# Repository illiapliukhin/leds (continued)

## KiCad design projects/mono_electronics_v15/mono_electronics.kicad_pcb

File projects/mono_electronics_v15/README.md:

# mono_electronics v15b: ESP32-S3 mono LED driver board (standalone KiCad project)

This folder is the self-contained, canonical copy of the v15 mono electronics board (PR #4). Open `mono_electronics.kicad_pro` in KiCad 10. The symbols (`symbols/`), footprints (`footprints/mono_electronics.pretty`) and 3D models (`3dmodels/`, via `${KIPRJMOD}`) are all local. The originals stay in `hardware/mono_schematic/` (schematic) and `hardware/mono_electronics/` (board), and are kept in sync.

## Spec summary
| | |
|---|---|
| Board | 148.0 × 99.5 mm, 4 layers, **1.6 mm JLC04161H-7628** (1 oz outer / 0.5 oz inner, ENIG), top-side assembly only, 4 × M2.5 plated holes, 3 fiducials |
| MCU | ESP32-S3FN8 (QFN-56), 40 MHz crystal, USB-C (HRO TYPE-C-31-M-12) with USBLC6-2SC6 ESD |
| Power in | USB VBUS_CONN → SMF12A TVS → TPS259531 eFuse (5.7 V OVP, R_ILM 2.7 k = 0.78 A) → BQ25185 charger/power path (ILIM 18 k ≈ 0.475 A, ISET 620 R) |
| Battery | 1S Li-ion on JST PH S3B-PH-SM4-TB; 0466002 2 A fuse; AO3401A reverse-battery P-FET; MAX17048 gauge |
| Rails | LED_4V1 = 4.24 V (TPS63802, FB 681k/91k); AON_3V3 (TLV75733P); LED_LOGIC_3V3 / AUDIO_3V3 (TPS22917 switches) |
| LED drive | 2 × MBI5124 (16 ch, 10 mA, Rext 1.82 k), 2 × 74HC154 row decoders, 32 × AO3403 row FETs, SN74LVC8T245 level shift; worst row drop ≈ 107 mV |
| Interfaces | 2 × 40-pin 0.5 mm FFC (Type B cable), installation variant: 2 × 2×20 1.27 mm box headers + 64 × PESD5V0S1BL; 4 × RS-485/sync ports (JST SH 6P, THVD1406); BMI270 IMU; MEMS mic |
| LED interface | See `docs/LED_INTERFACE_STANDARD.md` |

## Contents
- `mono_electronics.kicad_pro / .kicad_sch / .kicad_pcb`, `sheets/` (10 sub-sheets), `symbols/`, `footprints/`, `3dmodels/`, `sym-lib-table`, `fp-lib-table`
- `fab/`: Gerbers and Excellon drill (`fab/gerbers/`), JLCPCB BOM + CPL for the **wearable** and **installation** variants, annotated BOM, `README_FAB.md`, and `mono_electronics_v15_fab.zip` (the upload package)
- `drawings/`: schematic PDF, top assembly drawing PDF
- `renders/`: top / bottom / iso 3D renders
- `docs/`: MFG_AUDIT_v15 (manufacturing-standards audit and fixes), ABSMAX_REVIEW_v13, LED_INTERFACE_STANDARD, REWORK_LOG, LAST_CHANGES, PROZVONKA_v15 (continuity check), ERC_WAIVERS

## Verification (2026-10-12, KiCad 10.0.7 kicad-cli, run from this folder)
- `kicad-cli pcb drc --schematic-parity --severity-all mono_electronics.kicad_pcb`: **0 violations, 0 unconnected, 0 parity issues**. Board min clearance rule 0.127 mm. Zones refilled before plotting.
- `kicad-cli sch erc --severity-all mono_electronics.kicad_sch`: **0**
- Continuity 312/312 footprints (309 schematic parts + 3 board-only fiducials). Nets 224. All trace bends are arcs. No B-side parts.

## Known gaps
- No 3D model for J_BAT1 (JST S3B-PH-SM4-TB): there is none in the KiCad library.
- J_RH1/J_CH1 box header C42462832: stock ~125, so check it before ordering. Thin stock also on MIC1, Y1 and J_BAT1 (see fab/README_FAB.md).
- Check CPL rotations in the JLC preview: the CPL is raw KiCad output, with no JLC offsets applied.

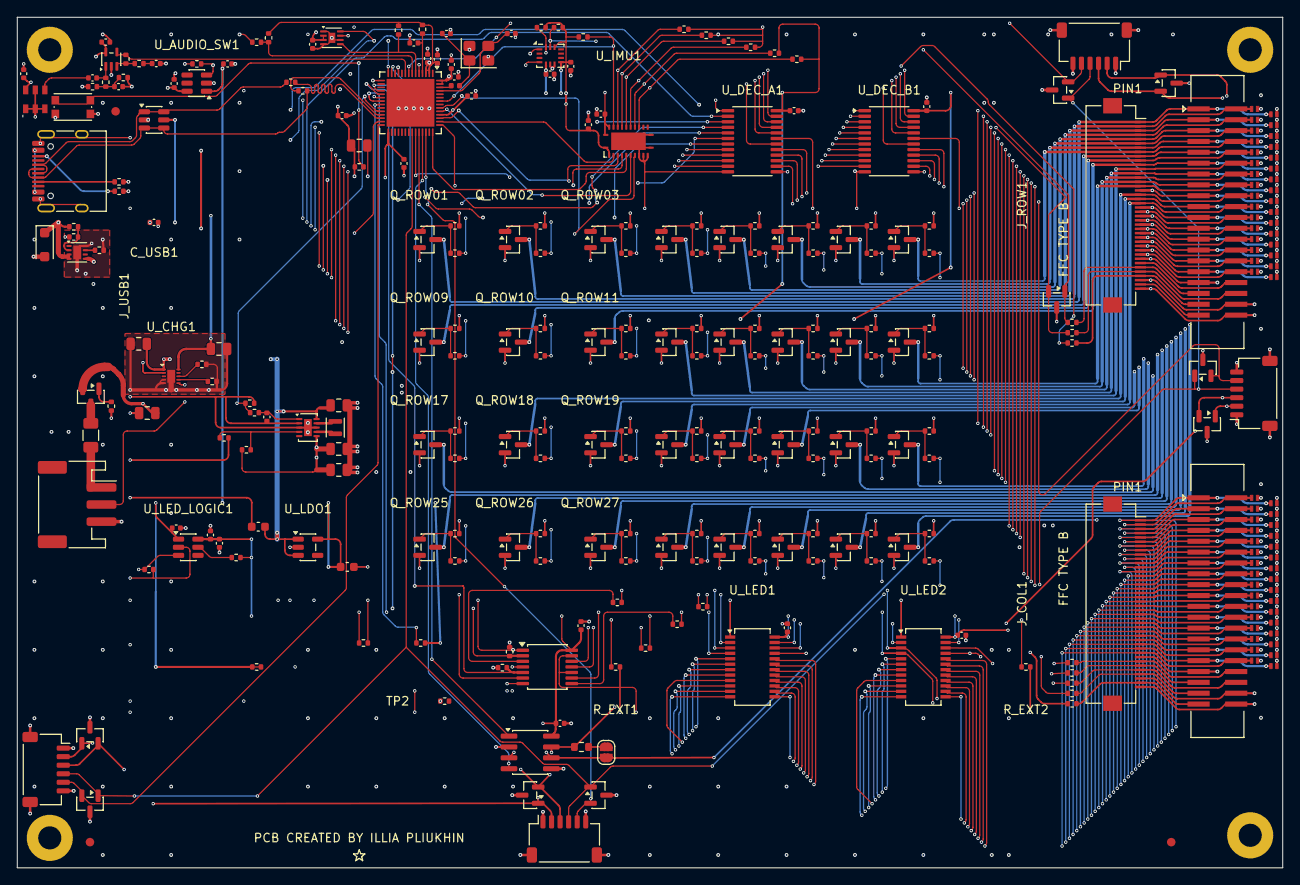
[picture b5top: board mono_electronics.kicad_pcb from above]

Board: 4 copper layers, 148.0 x 99.5 mm, 312 parts (0 on the bottom side), 223 nets.

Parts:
C_485: 100nF; C_0402_1005Metric
C_AC1: 1u; C_0402_1005Metric
C_ASW_IN1: 1u; C_0402_1005Metric
C_AUD1: 100n; C_0402_1005Metric
C_AUD_SW1: 1u; C_0402_1005Metric
C_B1: 4.7u; C_0402_1005Metric
C_BUF_V1: 100n; C_0402_1005Metric
C_CHG_BAT1: 10u; C_0805_2012Metric
C_CHG_IN1: 10u; C_0805_2012Metric
C_CHG_SYS1: 10u; C_0805_2012Metric
C_CHIP_PU1: 1u; C_0402_1005Metric
C_DECA_V1: 100n; C_0402_1005Metric
C_DECB_V1: 100n; C_0402_1005Metric
C_EN1: 10n; C_0402_1005Metric
C_GAUGE1: 100n; C_0402_1005Metric
C_GN1: 4.7u; C_0402_1005Metric
C_IMU_VDD1: 100n; C_0402_1005Metric
C_IMU_VIO1: 100n; C_0402_1005Metric
C_LDO_IN1: 1u; C_0603_1608Metric
C_LDO_OUT1: 1u; C_0603_1608Metric
C_LED1, C_LED2: 22u; C_0805_2012Metric
C_LED1_V1, C_LED2_V1: 100n; C_0402_1005Metric
C_LL1: 1u; C_0402_1005Metric
C_LL2: 100n; C_0402_1005Metric
C_LL_IN1: 1u; C_0402_1005Metric_SilkTrim
C_MCU1: 22u; C_0805_2012Metric
C_MCU_A2: 1u; C_0402_1005Metric
C_MCU_A3: 100n; C_0402_1005Metric
C_MCU_CPU1: 100n; C_0402_1005Metric
C_MCU_DA1: 100n; C_0402_1005Metric
C_MCU_DA2: 1u; C_0402_1005Metric
C_MCU_RTC1: 100n; C_0402_1005Metric
C_MCU_SPI1: 1u; C_0402_1005Metric
C_MIC1: 100n; C_0402_1005Metric
C_SYS1: 10u; C_0805_2012Metric
C_USB1: 100n; C_0402_1005Metric
C_XLAT_A1: 100n; C_0402_1005Metric
C_XLAT_B1: 100n; C_0402_1005Metric
C_XTAL1, C_XTAL2: 10p; C_0402_1005Metric
D_C01, D_C02, D_C03, D_C04, D_C05, D_C06, D_C07, D_C08, D_C09, D_C10, D_C11, D_C12, D_C13, D_C14, D_C15, D_C16, D_C17, D_C18, D_C19, D_C20, D_C21, D_C22, D_C23, D_C24, D_C25, D_C26, D_C27, D_C28, D_C29, D_C30, D_C31, D_C32: PESD5V0S1BL (DNP wearable); D_SOD-882
D_E_AB1: SM712; SOT-23
D_E_SP1: PESD3V3S2UT; SOT-23
D_ID1: PESD5V0S2BT; SOT-23
D_N_AB1: SM712; SOT-23
D_N_SP1: PESD3V3S2UT; SOT-23
D_R01, D_R02, D_R03, D_R04, D_R05, D_R06, D_R07, D_R08, D_R09, D_R10, D_R11, D_R12, D_R13, D_R14, D_R15, D_R16, D_R17, D_R18, D_R19, D_R20, D_R21, D_R22, D_R23, D_R24, D_R25, D_R26, D_R27, D_R28, D_R29, D_R30, D_R31, D_R32: PESD5V0S1BL (DNP wearable); D_SOD-882
D_S_AB1: SM712; SOT-23
D_S_SP1: PESD3V3S2UT; SOT-23
D_VBUS1: SMF12A; D_SOD-123F
D_W_AB1: SM712; SOT-23
D_W_SP1: PESD3V3S2UT; SOT-23
FID1, FID2, FID3: Fiducial; Fiducial_1mm_Mask2mm
F_BAT1: 0466002.NRHF 2A; Fuse_1206_3216Metric
H1, H2, H3, H4: M2.5; MountingHole_2.7mm_M2.5_Pad
JP_TERM1: TERM; SolderJumper-2_P1.3mm_Open_RoundedPad1.0x1.5mm
J_BAT1: S3B-PH-SM4-TB; JST_PH_S3B-PH-SM4-TB_1x03-1MP_P2.00mm_Horizontal
J_CH1: BH127VS-40P-H49 2x20 1.27mm box header (DNP weara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; BoxHeader_XFCN_BH127VS-40P-H49_2x20_P1.27mm_Vertical_SMD
J_COL1: FFC_40P_050_COL
J_PORT_E1: SM06B-SRSS-TB; JST_SH_SM06B-SRSS-TB_1x06-1MP_P1.00mm_Horizontal
J_PORT_N1: SM06B-SRSS-TB; JST_SH_SM06B-SRSS-TB_1x06-1MP_P1.00mm_Horizontal
J_PORT_S1: SM06B-SRSS-TB; JST_SH_SM06B-SRSS-TB_1x06-1MP_P1.00mm_Horizontal
J_PORT_W1: SM06B-SRSS-TB; JST_SH_SM06B-SRSS-TB_1x06-1MP_P1.00mm_Horizontal
J_RH1: BH127VS-40P-H49 2x20 1.27mm box header (DNP weara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; BoxHeader_XFCN_BH127VS-40P-H49_2x20_P1.27mm_Vertical_SMD
J_ROW1: FFC_40P_050_ROW
J_USB1: TYPE-C-31-M-12; USB_C_Receptacle_HRO_TYPE-C-31-M-12
L_LED1: DFE201612E-R47M; L_Murata_DFE201610P
L_XTAL1: 24nH; L_0402_1005Metric
MIC1: MA-HFA381-H13-1AF; MIC_Gettop_MA-HFA381_3.5x2.65mm
Q_BAT1: AO3401A; SOT-23
Q_ROW01, Q_ROW02, Q_ROW03, Q_ROW04, Q_ROW05, Q_ROW06, Q_ROW07, Q_ROW08, Q_ROW09, Q_ROW10, Q_ROW11, Q_ROW12, Q_ROW13, Q_ROW14, Q_ROW15, Q_ROW16, Q_ROW17, Q_ROW18, Q_ROW19, Q_ROW20, Q_ROW21, Q_ROW22, Q_ROW23, Q_ROW24, Q_ROW25, Q_ROW26, Q_ROW27, Q_ROW28, Q_ROW29, Q_ROW30, Q_ROW31, Q_ROW32: AO3403; SOT-23
R_ADDR0, R_ADDR1, R_ADDR2, R_ADDR3: 100k; R_0402_1005Metric
R_ALRT1: 10k; R_0402_1005Metric
R_AUD_PD1: 100k; R_0402_1005Metric
R_B1, R_B2: 100k; R_0402_1005Metric
R_BATG1: 10k; R_0402_1005Metric
R_BOOT0: 10k; R_0402_1005Metric
R_CC1, R_CC2: 5.1k; R_0402_1005Metric
R_CHIP_PU1: 10k; R_0402_1005Metric
R_CLK_PD1: 100k; R_0402_1005Metric
R_CLK_SER1: 22R; R_0402_1005Metric
R_ENA1: 47k; R_0402_1005Metric
R_ENB1: 47k; R_0402_1005Metric
R_EN_BOT1: 39k; R_0402_1005Metric
R_EN_PD1: 100k; R_0402_1005Metric
R_EN_SER1: 100k; R_0402_1005Metric
R_EN_TOP1: 100k; R_0402_1005Metric
R_EXP_3V1: 0R DNP; R_0402_1005Metric
R_EXP_CLK1: 33R DNP; R_0402_1005Metric
R_EXP_LE1: 33R DNP; R_0402_1005Metric
R_EXP_OE1: 33R DNP; R_0402_1005Metric
R_EXP_SDI1: 33R DNP; R_0402_1005Metric
R_EXT1, R_EXT2: 1.82k; R_0402_1005Metric
R_F1: 100k; R_0402_1005Metric_SilkTrim
R_FB_BOT1: 91k; R_0402_1005Metric
R_FB_TOP1: 681k; R_0402_1005Metric
R_G01, R_G02, R_G03, R_G04, R_G05, R_G06, R_G07, R_G08, R_G09, R_G10, R_G11, R_G12, R_G13, R_G14, R_G15, R_G16, R_G17, R_G18, R_G19, R_G20, R_G21, R_G22, R_G23, R_G24, R_G25, R_G26, R_G27, R_G28, R_G29, R_G30, R_G31, R_G32: 33R; R_0402_1005Metric
R_GN1: 2.2k; R_0402_1005Metric
R_ID_3V1: 100R; R_0402_1005Metric
R_ID_SCL1: 33R; R_0402_1005Metric
R_ID_SDA1: 33R; R_0402_1005Metric
R_ILIM1: 18k; R_0402_1005Metric
R_ILM1: 2.7k; R_0402_1005Metric
R_INB1: 100k; R_0402_1005Metric
R_ISET1: 600R; R_0402_1005Metric
R_LE_PD1: 100k; R_0402_1005Metric
R_LE_SER1: 22R; R_0402_1005Metric
R_LOGIC_PD1: 100k; R_0402_1005Metric
R_OE_PU1: 47k; R_0402_1005Metric
R_OE_YPU1: 47k; R_0402_1005Metric
R_PU01, R_PU02, R_PU03, R_PU04, R_PU05, R_PU06, R_PU07, R_PU08, R_PU09, R_PU10, R_PU11, R_PU12, R_PU13, R_PU14, R_PU15, R_PU16, R_PU17, R_PU18, R_PU19, R_PU20, R_PU21, R_PU22, R_PU23, R_PU24, R_PU25, R_PU26, R_PU27, R_PU28, R_PU29, R_PU30, R_PU31, R_PU32: 47k; R_0402_1005Metric
R_QOD1: 1k; R_0402_1005Metric
R_SCL1: 4.7k; R_0402_1005Metric
R_SDA1: 4.7k; R_0402_1005Metric
R_SDI_PD1: 100k; R_0402_1005Metric
R_SDI_SER1: 22R; R_0402_1005Metric
R_TERM1: 120R; R_0603_1608Metric
R_TH1: 10k 1%; R_0402_1005Metric
R_USB_N1: 22R; R_0402_1005Metric
R_USB_P1: 22R; R_0402_1005Metric
R_XOE1: 10k; R_0402_1005Metric
SW1: KMR2; SW_Push_1P1T_NO_CK_KMR2
TH_PCB1: NTC 10k B3435; R_0402_1005Metric
TP1: AON_3V3; R_0402_1005Metric
TP2: GND; R_0402_1005Metric
U1: ESP32-S3FN8; QFN-56-1EP_7x7mm_P0.4mm_EP5.6x5.6mm
U_485: THVD1406DR; SOIC-8_3.9x4.9mm_P1.27mm
U_AUDIO1: TLV9001IDCKR; SOT-353_SC-70-5
U_AUDIO_SW1: TPS22917; SOT-23-6
U_CHG1: BQ25185; Texas_DLH0010A_WSON-10-1EP_2x2mm_P0.4mm_EP0.9x1.5mm
U_DEC_A1: 74HC154; TSSOP-24_4.4x7.8mm_P0.65mm
U_DEC_B1: 74HC154; TSSOP-24_4.4x7.8mm_P0.65mm
U_ESD1: USBLC6-2SC6; SOT-23-6
U_GAUGE1: MAX17048G+T10; TDFN-8-1EP_2x2mm_P0.5mm_EP0.8x1.2mm
U_IMU1: BMI270; Bosch_LGA-14_3x2.5mm_P0.5mm
U_LDO1: TLV75733PDBVR; SOT-23-5
U_LED1, U_LED2: MBI5124GP-B; SSOP-24_3.9x8.7mm_P0.635mm
U_LED_BUF1: SN74LV125A; TSSOP-14_4.4x5mm_P0.65mm
U_LED_LOGIC1: TPS22917; SOT-23-6
U_LED_PWR1: TPS63802DLAR; TDFN-10-1EP_2x3mm_P0.5mm_EP0.9x2mm
U_OVP1: TPS259531DSGR; Texas_DSG0008A_WSON-8-1EP_2x2mm_P0.5mm_EP0.9x1.6mm
U_ROW_XLAT1: SN74LVC8T245RHLR; Texas_RHL0024A_VQFN-24-1EP_3.5x5.5mm_P0.5mm_EP2.05x4.05mm
Y1: L327S400H11L; Crystal_SMD_3225-4Pin_3.2x2.5mm

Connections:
AON_3V3: C_ASW_IN1.1, C_IMU_VDD1.1, C_IMU_VIO1.1, C_LDO_OUT1.1, C_LL_IN1.1, C_MCU1.1, C_MCU_A2.1, C_MCU_A3.1, C_MCU_CPU1.1, C_MCU_DA1.1, C_MCU_DA2.1, C_MCU_RTC1.1, C_MCU_SPI1.1, C_XLAT_A1.1, R_ALRT1.2, R_BOOT0.1, R_CHIP_PU1.2, R_ID_3V1.1, R_OE_PU1.2, R_SCL1.2, R_SDA1.2, R_TH1.2, R_XOE1.1, TP1.1, TP1.2, U1.2, U1.3, U1.20, U1.29, U1.46, U1.55, U1.56, U_AUDIO_SW1.1, U_IMU1.5, U_IMU1.8, U_IMU1.12, U_LDO1.5, U_LED_LOGIC1.1, U_ROW_XLAT1.1, U_ROW_XLAT1.2
AUDIO_3V3: C_AUD1.1, C_AUD_SW1.1, C_MIC1.2, MIC1.6, R_B1.1, U_AUDIO1.5, U_AUDIO_SW1.6
AUDIO_ADC: R_F1.2, U1.9, U_AUDIO1.4
AUDIO_EN: R_AUD_PD1.1, U1.11, U_AUDIO_SW1.3
AUD_BIAS: C_B1.1, R_B1.2, R_B2.1, R_INB1.1
AUD_FB: R_F1.1, R_GN1.1, U_AUDIO1.3
AUD_GC: C_GN1.1, R_GN1.2
AUD_INP: C_AC1.2, R_INB1.2, U_AUDIO1.1
BAT_FUSE: F_BAT1.2, Q_BAT1.3
BAT_GATE: Q_BAT1.1, R_BATG1.1
BAT_PACK: F_BAT1.1, J_BAT1.1
BAT_RAW: C_CHG_BAT1.2, C_GAUGE1.2, Q_BAT1.2, U_CHG1.2, U_GAUGE1.2, U_GAUGE1.3
CHIP_PU: C_CHIP_PU1.1, R_CHIP_PU1.1, U1.4
COL_01: D_C01.1, J_CH1.1, J_COL1.1, U_LED1.5
COL_02: D_C02.1, J_CH1.2, J_COL1.2, U_LED1.6
COL_03: D_C03.1, J_CH1.3, J_COL1.3, U_LED1.7
COL_04: D_C04.1, J_CH1.4, J_COL1.4, U_LED1.8
COL_05: D_C05.1, J_CH1.5, J_COL1.5, U_LED1.9
COL_06: D_C06.1, J_CH1.6, J_COL1.6, U_LED1.10
COL_07: D_C07.1, J_CH1.7, J_COL1.7, U_LED1.11
COL_08: D_C08.1, J_CH1.8, J_COL1.8, U_LED1.12
COL_09: D_C09.1, J_CH1.9, J_COL1.9, U_LED1.13
COL_10: D_C10.1, J_CH1.10, J_COL1.10, U_LED1.14
COL_11: D_C11.1, J_CH1.11, J_COL1.11, U_LED1.15
COL_12: D_C12.1, J_CH1.12, J_COL1.12, U_LED1.16
COL_13: D_C13.1, J_CH1.13, J_COL1.13, U_LED1.17
COL_14: D_C14.1, J_CH1.14, J_COL1.14, U_LED1.18
COL_15: D_C15.1, J_CH1.15, J_COL1.15, U_LED1.19
COL_16: D_C16.1, J_CH1.16, J_COL1.16, U_LED1.20
COL_17: D_C17.1, J_CH1.17, J_COL1.17, U_LED2.5
COL_18: D_C18.1, J_CH1.18, J_COL1.18, U_LED2.6
COL_19: D_C19.1, J_CH1.19, J_COL1.19, U_LED2.7
COL_20: D_C20.1, J_CH1.20, J_COL1.20, U_LED2.8
COL_21: D_C21.1, J_CH1.21, J_COL1.21, U_LED2.9
COL_22: D_C22.1, J_CH1.22, J_COL1.22, U_LED2.10
COL_23: D_C23.1, J_CH1.23, J_COL1.23, U_LED2.11
COL_24: D_C24.1, J_CH1.24, J_COL1.24, U_LED2.12
COL_25: D_C25.1, J_CH1.25, J_COL1.25, U_LED2.13
COL_26: D_C26.1, J_CH1.26, J_COL1.26, U_LED2.14
COL_27: D_C27.1, J_CH1.27, J_COL1.27, U_LED2.15
COL_28: D_C28.1, J_CH1.28, J_COL1.28, U_LED2.16
COL_29: D_C29.1, J_CH1.29, J_COL1.29, U_LED2.17
COL_30: D_C30.1, J_CH1.30, J_COL1.30, U_LED2.18
COL_31: D_C31.1, J_CH1.31, J_COL1.31, U_LED2.19
COL_32: D_C32.1, J_CH1.32, J_COL1.32, U_LED2.20
DEC_A_EN_N: U1.47, U_ROW_XLAT1.7
DEC_A_EN_N_4V: R_ENA1.1, U_DEC_A1.18, U_ROW_XLAT1.17
DEC_B_EN_N: U1.48, U_ROW_XLAT1.8
DEC_B_EN_N_4V: R_ENB1.1, U_DEC_B1.18, U_ROW_XLAT1.16
EXP_3V3: J_CH1.39, J_COL1.39, R_EXP_3V1.2
EXP_CLK: J_CH1.35, J_COL1.35, R_EXP_CLK1.2
EXP_LE: J_CH1.36, J_COL1.36, R_EXP_LE1.2
EXP_OE: J_CH1.37, J_COL1.37, R_EXP_OE1.2
EXP_SDI: J_CH1.34, J_COL1.34, R_EXP_SDI1.2
FRAME_SYNC: D_E_SP1.1, D_N_SP1.1, D_S_SP1.1, D_W_SP1.1, J_PORT_E1.4, J_PORT_N1.4, J_PORT_S1.4, J_PORT_W1.4, U1.36
GAUGE_ALRT_N: R_ALRT1.1, U1.6, U_GAUGE1.5
GND: C_485.2, C_ASW_IN1.2, C_AUD1.2, C_AUD_SW1.2, C_B1.2, C_BUF_V1.2, C_CHG_BAT1.1, C_CHG_IN1.2, C_CHG_SYS1.1, C_CHIP_PU1.2, C_DECA_V1.2, C_DECB_V1.2, C_EN1.2, C_GAUGE1.1, C_GN1.2, C_IMU_VDD1.2, C_IMU_VIO1.2, C_LDO_IN1.1, C_LDO_OUT1.2, C_LED1.2, C_LED1_V1.2, C_LED2.2, C_LED2_V1.2, C_LL1.2, C_LL2.2, C_LL_IN1.2, C_MCU1.2, C_MCU_A2.2, C_MCU_A3.2, C_MCU_CPU1.2, C_MCU_DA1.2, C_MCU_DA2.2, C_MCU_RTC1.2, C_MCU_SPI1.2, C_MIC1.1, C_SYS1.2, C_USB1.2, C_XLAT_A1.2, C_XLAT_B1.2, C_XTAL1.2, C_XTAL2.2, D_C01.2, D_C02.2, D_C03.2, D_C04.2, D_C05.2, D_C06.2, D_C07.2, D_C08.2, D_C09.2, D_C10.2, D_C11.2, D_C12.2, D_C13.2, D_C14.2, D_C15.2, D_C16.2, D_C17.2, D_C18.2, D_C19.2, D_C20.2, D_C21.2, D_C22.2, D_C23.2, D_C24.2, D_C25.2, D_C26.2, D_C27.2, D_C28.2, D_C29.2, D_C30.2, D_C31.2, D_C32.2, D_E_AB1.3, D_E_SP1.3, D_ID1.3, D_N_AB1.3, D_N_SP1.3, D_R01.2, D_R02.2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
GPIO0_BOOT: R_BOOT0.2, SW1.1, U1.5
ID_3V3: J_RH1.37, J_ROW1.37, R_ID_3V1.2
ID_SCL: J_RH1.36, J_ROW1.36, R_ID_SCL1.2
ID_SDA: J_RH1.35, J_ROW1.35, R_ID_SDA1.2
ILIM_VSET: R_ILIM1.1, U_CHG1.7
IMU_INT1: U1.15, U_IMU1.4
IMU_SCL: D_ID1.2, R_ID_SCL1.1, R_SCL1.1, U1.14, U_GAUGE1.7, U_IMU1.13
IMU_SDA: D_ID1.1, R_ID_SDA1.1, R_SDA1.1, U1.13, U_GAUGE1.8, U_IMU1.14
ISET: R_ISET1.1, U_CHG1.8
LED_4V1: C_DECA_V1.1, C_DECB_V1.1, C_LED1.1, C_LED2.1, C_XLAT_B1.1, Q_ROW01.2, Q_ROW02.2, Q_ROW03.2, Q_ROW04.2, Q_ROW05.2, Q_ROW06.2, Q_ROW07.2, Q_ROW08.2, Q_ROW09.2, Q_ROW10.2, Q_ROW11.2, Q_ROW12.2, Q_ROW13.2, Q_ROW14.2, Q_ROW15.2, Q_ROW16.2, Q_ROW17.2, Q_ROW18.2, Q_ROW19.2, Q_ROW20.2, Q_ROW21.2, Q_ROW22.2, Q_ROW23.2, Q_ROW24.2, Q_ROW25.2, Q_ROW26.2, Q_ROW27.2, Q_ROW28.2, Q_ROW29.2, Q_ROW30.2, Q_ROW31.2, Q_ROW32.2, R_ENA1.2, R_ENB1.2, R_FB_TOP1.1, R_PU01.2, R_PU02.2, R_PU03.2, R_PU04.2, R_PU05.2, R_PU06.2, R_PU07.2, R_PU08.2, R_PU09.2, R_PU10.2, R_PU11.2, R_PU12.2, R_PU13.2, R_PU14.2, R_PU15.2, R_PU16.2, R_PU17.2, R_PU18.2, R_PU19.2, R_PU20.2, R_PU21.2, R_PU22.2, R_PU23.2, R_PU24.2, R_PU25.2, R_PU26.2, R_PU27.2, R_PU28.2, R_PU29.2, R_PU30.2, R_PU31.2, R_PU32.2, U_DEC_A1.24, U_DEC_B1.24, U_LED_PWR1.6, U_ROW_XLAT1.23, U_ROW_XLAT1.24
LED_CLK: R_CLK_PD1.1, U1.18, U_LED_BUF1.2
LED_CLK_PRE: R_CLK_SER1.1, U_LED_BUF1.3
LED_CLK_Y: R_CLK_SER1.2, R_EXP_CLK1.1, U_LED1.3, U_LED2.3
LED_EN: R_EN_PD1.1, R_EN_SER1.1, U1.24
LED_EN_RC: C_EN1.1, R_EN_SER1.2, U_LED_PWR1.1
LED_FB: R_FB_BOT1.1, R_FB_TOP1.2, U_LED_PWR1.4
LED_LE: R_LE_PD1.1, U1.21, U_LED_BUF1.9
LED_LE_PRE: R_LE_SER1.1, U_LED_BUF1.8
LED_LE_Y: R_EXP_LE1.1, R_LE_SER1.2, U_LED1.4, U_LED2.4
LED_LOGIC_3V3: C_485.1, C_BUF_V1.1, C_LED1_V1.1, C_LED2_V1.1, C_LL1.1, C_LL2.1, R_EXP_3V1.1, R_OE_YPU1.2, R_QOD1.2, U_485.3, U_485.8, U_LED1.24, U_LED2.24, U_LED_BUF1.14, U_LED_LOGIC1.6
LED_LOGIC_EN: R_LOGIC_PD1.1, U1.27, U_LED_LOGIC1.3
LED_OE_N: R_OE_PU1.1, U1.22, U_LED_BUF1.12
LED_OE_Y: R_EXP_OE1.1, R_OE_YPU1.1, U_LED1.21, U_LED2.21, U_LED_BUF1.11
LED_QOD: R_QOD1.1, U_LED_LOGIC1.5
LED_SDI: R_SDI_PD1.1, U1.19, U_LED_BUF1.5
LED_SDI_PRE: R_SDI_SER1.1, U_LED_BUF1.6
LED_SDI_Y: R_SDI_SER1.2, U_LED1.2
LED_SDO: U_LED1.22, U_LED2.2
LED_SDO2: R_EXP_SDI1.1, U_LED2.22
MIC_OUT: C_AC1.1, MIC1.4
OVP_EN: R_EN_BOT1.1, R_EN_TOP1.2, U_OVP1.2
OVP_ILM: R_ILM1.1, U_OVP1.7
PRES_E: D_E_SP1.2, J_PORT_E1.5, U1.37
PRES_N: D_N_SP1.2, J_PORT_N1.5, U1.8
PRES_S: D_S_SP1.2, J_PORT_S1.5, U1.40
PRES_W: D_W_SP1.2, J_PORT_W1.5, U1.28
REXT1: R_EXT1.1, U_LED1.23
REXT2: R_EXT2.1, U_LED2.23
ROW_01_ANODE: D_R01.1, J_RH1.1, J_ROW1.1, Q_ROW01.3
ROW_01_GATE: Q_ROW01.1, R_G01.1, R_PU01.1
ROW_01_Y: R_G01.2, U_DEC_A1.1
ROW_02_ANODE: D_R02.1, J_RH1.2, J_ROW1.2, Q_ROW02.3
ROW_02_GATE: Q_ROW02.1, R_G02.1, R_PU02.1
ROW_02_Y: R_G02.2, U_DEC_A1.2
ROW_03_ANODE: D_R03.1, J_RH1.3, J_ROW1.3, Q_ROW03.3
ROW_03_GATE: Q_ROW03.1, R_G03.1, R_PU03.1
ROW_03_Y: R_G03.2, U_DEC_A1.3
ROW_04_ANODE: D_R04.1, J_RH1.4, J_ROW1.4, Q_ROW04.3
ROW_04_GATE: Q_ROW04.1, R_G04.1, R_PU04.1
ROW_04_Y: R_G04.2, U_DEC_A1.4
ROW_05_ANODE: D_R05.1, J_RH1.5, J_ROW1.5, Q_ROW05.3
ROW_05_GATE: Q_ROW05.1, R_G05.1, R_PU05.1
ROW_05_Y: R_G05.2, U_DEC_A1.5
ROW_06_ANODE: D_R06.1, J_RH1.6, J_ROW1.6, Q_ROW06.3
ROW_06_GATE: Q_ROW06.1, R_G06.1, R_PU06.1
ROW_06_Y: R_G06.2, U_DEC_A1.6
ROW_07_ANODE: D_R07.1, J_RH1.7, J_ROW1.7, Q_ROW07.3
ROW_07_GATE: Q_ROW07.1, R_G07.1, R_PU07.1
ROW_07_Y: R_G07.2, U_DEC_A1.7
ROW_08_ANODE: D_R08.1, J_RH1.8, J_ROW1.8, Q_ROW08.3
ROW_08_GATE: Q_ROW08.1, R_G08.1, R_PU08.1
ROW_08_Y: R_G08.2, U_DEC_A1.8
ROW_09_ANODE: D_R09.1, J_RH1.9, J_ROW1.9, Q_ROW09.3
ROW_09_GATE: Q_ROW09.1, R_G09.1, R_PU09.1
ROW_09_Y: R_G09.2, U_DEC_A1.9
ROW_10_ANODE: D_R10.1, J_RH1.10, J_ROW1.10, Q_ROW10.3
ROW_10_GATE: Q_ROW10.1, R_G10.1, R_PU10.1
ROW_10_Y: R_G10.2, U_DEC_A1.10
ROW_11_ANODE: D_R11.1, J_RH1.11, J_ROW1.11, Q_ROW11.3
ROW_11_GATE: Q_ROW11.1, R_G11.1, R_PU11.1
ROW_11_Y: R_G11.2, U_DEC_A1.11
ROW_12_ANODE: D_R12.1, J_RH1.12, J_ROW1.12, Q_ROW12.3
ROW_12_GATE: Q_ROW12.1, R_G12.1, R_PU12.1
ROW_12_Y: R_G12.2, U_DEC_A1.13
ROW_13_ANODE: D_R13.1, J_RH1.13, J_ROW1.13, Q_ROW13.3
ROW_13_GATE: Q_ROW13.1, R_G13.1, R_PU13.1
ROW_13_Y: R_G13.2, U_DEC_A1.14
ROW_14_ANODE: D_R14.1, J_RH1.14, J_ROW1.14, Q_ROW14.3
ROW_14_GATE: Q_ROW14.1, R_G14.1, R_PU14.1
ROW_14_Y: R_G14.2, U_DEC_A1.15
ROW_15_ANODE: D_R15.1, J_RH1.15, J_ROW1.15, Q_ROW15.3
ROW_15_GATE: Q_ROW15.1, R_G15.1, R_PU15.1
ROW_15_Y: R_G15.2, U_DEC_A1.16
ROW_16_ANODE: D_R16.1, J_RH1.16, J_ROW1.16, Q_ROW16.3
ROW_16_GATE: Q_ROW16.1, R_G16.1, R_PU16.1
ROW_16_Y: R_G16.2, U_DEC_A1.17
ROW_17_ANODE: D_R17.1, J_RH1.17, J_ROW1.17, Q_ROW17.3
ROW_17_GATE: Q_ROW17.1, R_G17.1, R_PU17.1
ROW_17_Y: R_G17.2, U_DEC_B1.1
ROW_18_ANODE: D_R18.1, J_RH1.18, J_ROW1.18, Q_ROW18.3
ROW_18_GATE: Q_ROW18.1, R_G18.1, R_PU18.1
ROW_18_Y: R_G18.2, U_DEC_B1.2
ROW_19_ANODE: D_R19.1, J_RH1.19, J_ROW1.19, Q_ROW19.3
ROW_19_GATE: Q_ROW19.1, R_G19.1, R_PU19.1
ROW_19_Y: R_G19.2, U_DEC_B1.3
ROW_20_ANODE: D_R20.1, J_RH1.20, J_ROW1.20, Q_ROW20.3
ROW_20_GATE: Q_ROW20.1, R_G20.1, R_PU20.1
ROW_20_Y: R_G20.2, U_DEC_B1.4
ROW_21_ANODE: D_R21.1, J_RH1.21, J_ROW1.21, Q_ROW21.3
ROW_21_GATE: Q_ROW21.1, R_G21.1, R_PU21.1
ROW_21_Y: R_G21.2, U_DEC_B1.5
ROW_22_ANODE: D_R22.1, J_RH1.22, J_ROW1.22, Q_ROW22.3
ROW_22_GATE: Q_ROW22.1, R_G22.1, R_PU22.1
ROW_22_Y: R_G22.2, U_DEC_B1.6
ROW_23_ANODE: D_R23.1, J_RH1.23, J_ROW1.23, Q_ROW23.3
ROW_23_GATE: Q_ROW23.1, R_G23.1, R_PU23.1
ROW_23_Y: R_G23.2, U_DEC_B1.7
ROW_24_ANODE: D_R24.1, J_RH1.24, J_ROW1.24, Q_ROW24.3
ROW_24_GATE: Q_ROW24.1, R_G24.1, R_PU24.1
ROW_24_Y: R_G24.2, U_DEC_B1.8
ROW_25_ANODE: D_R25.1, J_RH1.25, J_ROW1.25, Q_ROW25.3
ROW_25_GATE: Q_ROW25.1, R_G25.1, R_PU25.1
ROW_25_Y: R_G25.2, U_DEC_B1.9
ROW_26_ANODE: D_R26.1, J_RH1.26, J_ROW1.26, Q_ROW26.3
ROW_26_GATE: Q_ROW26.1, R_G26.1, R_PU26.1
ROW_26_Y: R_G26.2, U_DEC_B1.10
ROW_27_ANODE: D_R27.1, J_RH1.27, J_ROW1.27, Q_ROW27.3
ROW_27_GATE: Q_ROW27.1, R_G27.1, R_PU27.1
ROW_27_Y: R_G27.2, U_DEC_B1.11
ROW_28_ANODE: D_R28.1, J_RH1.28, J_ROW1.28, Q_ROW28.3
ROW_28_GATE: Q_ROW28.1, R_G28.1, R_PU28.1
ROW_28_Y: R_G28.2, U_DEC_B1.13
ROW_29_ANODE: D_R29.1, J_RH1.29, J_ROW1.29, Q_ROW29.3
ROW_29_GATE: Q_ROW29.1, R_G29.1, R_PU29.1
ROW_29_Y: R_G29.2, U_DEC_B1.14
ROW_30_ANODE: D_R30.1, J_RH1.30, J_ROW1.30, Q_ROW30.3
ROW_30_GATE: Q_ROW30.1, R_G30.1, R_PU30.1
ROW_30_Y: R_G30.2, U_DEC_B1.15
ROW_31_ANODE: D_R31.1, J_RH1.31, J_ROW1.31, Q_ROW31.3
ROW_31_GATE: Q_ROW31.1, R_G31.1, R_PU31.1
ROW_31_Y: R_G31.2, U_DEC_B1.16
ROW_32_ANODE: D_R32.1, J_RH1.32, J_ROW1.32, Q_ROW32.3
ROW_32_GATE: Q_ROW32.1, R_G32.1, R_PU32.1
ROW_32_Y: R_G32.2, U_DEC_B1.17
ROW_A0: U1.44, U_ROW_XLAT1.3
ROW_A0_4V: R_ADDR0.1, U_DEC_A1.23, U_DEC_B1.23, U_ROW_XLAT1.21
ROW_A1: U1.45, U_ROW_XLAT1.4
ROW_A1_4V: R_ADDR1.1, U_DEC_A1.22, U_DEC_B1.22, U_ROW_XLAT1.20
ROW_A2: U1.43, U_ROW_XLAT1.5
ROW_A2_4V: R_ADDR2.1, U_DEC_A1.21, U_DEC_B1.21, U_ROW_XLAT1.19
ROW_A3: U1.42, U_ROW_XLAT1.6
ROW_A3_4V: R_ADDR3.1, U_DEC_A1.20, U_DEC_B1.20, U_ROW_XLAT1.18
ROW_SPARE_34: J_RH1.34, J_ROW1.34
ROW_SPARE_39: J_RH1.39, J_ROW1.39
ROW_XLAT_OE_N: R_XOE1.2, U1.50, U_ROW_XLAT1.22
RS485_A: D_E_AB1.1, D_N_AB1.1, D_S_AB1.1, D_W_AB1.1, JP_TERM1.1, J_PORT_E1.2, J_PORT_N1.2, J_PORT_S1.2, J_PORT_W1.2, U_485.6
RS485_B: D_E_AB1.2, D_N_AB1.2, D_S_AB1.2, D_W_AB1.2, J_PORT_E1.3, J_PORT_N1.3, J_PORT_S1.3, J_PORT_W1.3, R_TERM1.1, U_485.7
RS485_RX: U1.38, U_485.1
RS485_TX: U1.39, U_485.4
SW_L1: L_LED1.2, U_LED_PWR1.9
SW_L2: L_LED1.1, U_LED_PWR1.7
SYS: C_CHG_SYS1.2, C_LDO_IN1.2, C_SYS1.1, U_CHG1.1, U_LDO1.1, U_LDO1.3, U_LED_PWR1.10
TERM_MID: JP_TERM1.2, R_TERM1.2
TH_ADC: R_TH1.1, TH_PCB1.2, U1.7
TS_MR: J_BAT1.2, U_CHG1.6
USB_CC1: J_USB1.A5, R_CC1.1
USB_CC2: J_USB1.B5, R_CC2.1
USB_D_N: J_USB1.A7, J_USB1.B7, R_USB_N1.1, U_ESD1.3, U_ESD1.4
USB_D_N_MCU: R_USB_N1.2, U1.25
USB_D_P: J_USB1.A6, J_USB1.B6, R_USB_P1.1, U_ESD1.1, U_ESD1.6
USB_D_P_MCU: R_USB_P1.2, U1.26
VBUS: C_CHG_IN1.1, C_USB1.1, U_CHG1.10, U_ESD1.5, U_OVP1.5
VBUS_CONN: D_VBUS1.1, J_USB1.A4, J_USB1.A9, J_USB1.B4, J_USB1.B9, R_EN_TOP1.1, U_OVP1.3, U_OVP1.4
XTAL_N: C_XTAL2.1, U1.53, Y1.3
XTAL_P: C_XTAL1.1, L_XTAL1.2, Y1.1
XTAL_P_MCU: L_XTAL1.1, U1.54

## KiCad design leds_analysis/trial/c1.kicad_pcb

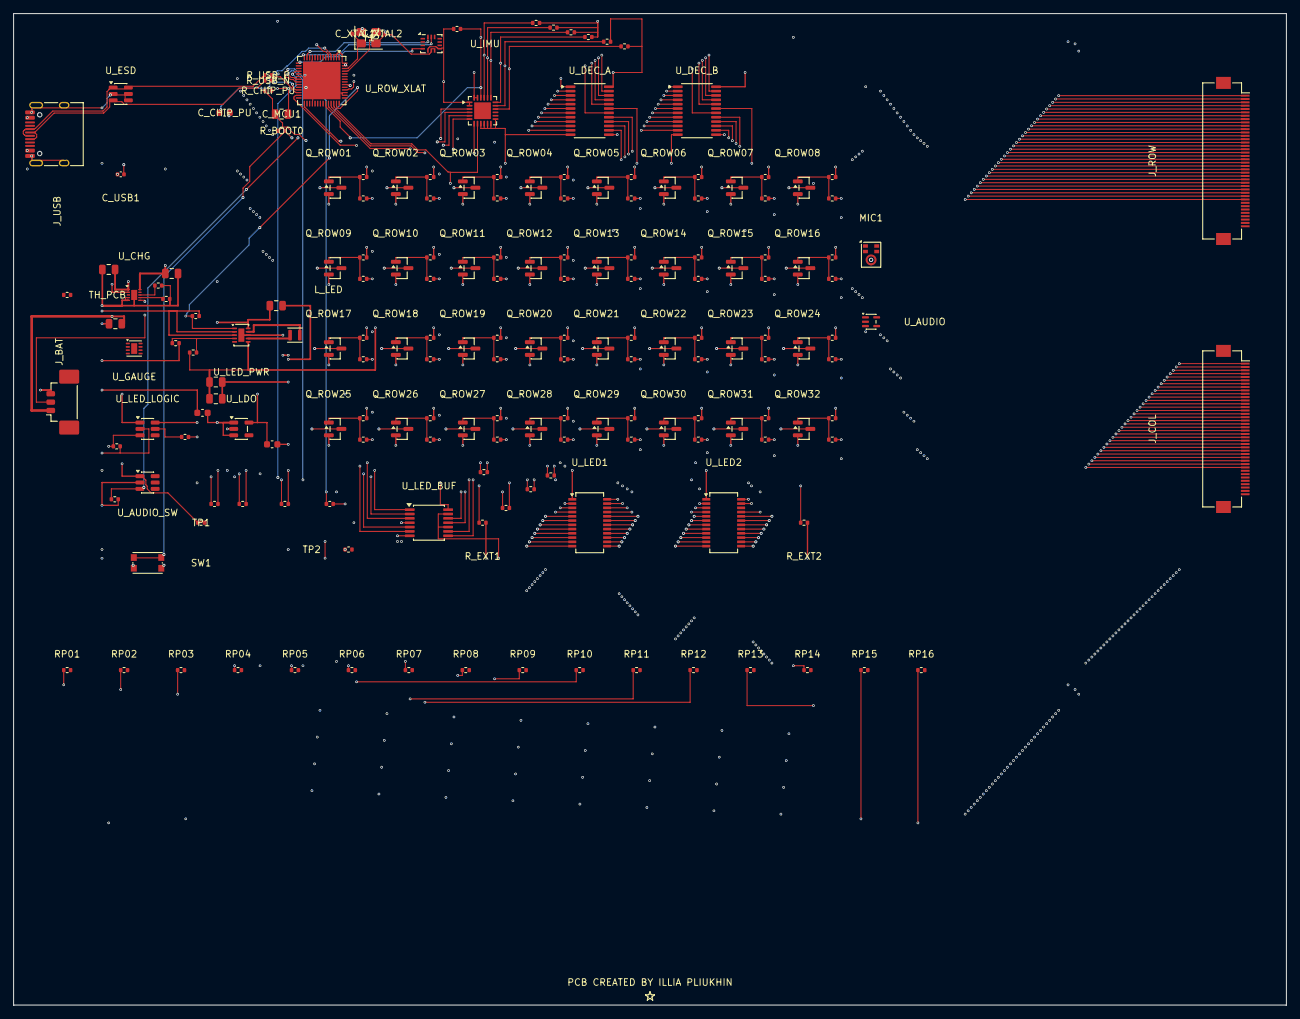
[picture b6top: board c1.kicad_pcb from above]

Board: 4 copper layers, 190.0 x 148.0 mm, 181 parts (0 on the bottom side), 183 nets.

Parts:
C_CHG_BAT: 10u; C_0805_2012Metric
C_CHG_IN: 10u; C_0805_2012Metric
C_CHG_SYS: 10u; C_0805_2012Metric
C_CHIP_PU: 1u; C_0603_1608Metric
C_LDO_IN: 1u; C_0603_1608Metric
C_LDO_OUT: 1u; C_0603_1608Metric
C_LED1, C_LED2: 22u; C_0805_2012Metric
C_MCU1: 10u; C_0805_2012Metric
C_SYS: 10u; C_0805_2012Metric
C_USB1: 100n; C_0402_1005Metric
C_XTAL1, C_XTAL2: 10p; C_0402_1005Metric
J_BAT: 53398-0371; Molex_PicoBlade_53398-0371_1x03-1MP_P1.25mm_Vertical
J_COL: FFC_40P_050_COL
J_ROW: FFC_40P_050_ROW
J_USB: USB4105; USB_C_Receptacle_HRO_TYPE-C-31-M-12
L_LED: DFE201612E-R47M; L_Murata_DFE201610P
MIC1: MA-HFA381; Knowles_LGA-5_3.5x2.65mm
Q_ROW01, Q_ROW02, Q_ROW03, Q_ROW04, Q_ROW05, Q_ROW06, Q_ROW07, Q_ROW08, Q_ROW09, Q_ROW10, Q_ROW11, Q_ROW12, Q_ROW13, Q_ROW14, Q_ROW15, Q_ROW16, Q_ROW17, Q_ROW18, Q_ROW19, Q_ROW20, Q_ROW21, Q_ROW22, Q_ROW23, Q_ROW24, Q_ROW25, Q_ROW26, Q_ROW27, Q_ROW28, Q_ROW29, Q_ROW30, Q_ROW31, Q_ROW32: AO3403; SOT-23
RP01: IMU_SDA; R_0402_1005Metric
RP02: IMU_SCL; R_0402_1005Metric
RP03: IMU_INT1; R_0402_1005Metric
RP04: LED_CLK; R_0402_1005Metric
RP05: LED_SDI; R_0402_1005Metric
RP06: LED_LE; R_0402_1005Metric
RP07: LED_OE_N; R_0402_1005Metric
RP08: ROW_A0; R_0402_1005Metric
RP09: ROW_A1; R_0402_1005Metric
RP10: ROW_A2; R_0402_1005Metric
RP11: ROW_A3; R_0402_1005Metric
RP12: DEC_A_EN_N; R_0402_1005Metric
RP13: DEC_B_EN_N; R_0402_1005Metric
RP14: ROW_XLAT_OE_N; R_0402_1005Metric
RP15: LED_EN; R_0402_1005Metric
RP16: LED_LOGIC_EN; R_0402_1005Metric
R_ADDR0, R_ADDR1, R_ADDR2, R_ADDR3: 100k; R_0402_1005Metric
R_AUD_PD: 100k; R_0402_1005Metric
R_BOOT0: 10k; R_0402_1005Metric
R_CHIP_PU: 10k; R_0402_1005Metric
R_CLK_PD: 100k; R_0402_1005Metric
R_CLK_SER: 22R; R_0402_1005Metric
R_ENA: 47k; R_0402_1005Metric
R_ENB: 47k; R_0402_1005Metric
R_EN_PD: 100k; R_0402_1005Metric
R_EXT1, R_EXT2: 1.82k; R_0402_1005Metric
R_FB_BOT: 91k; R_0402_1005Metric
R_FB_TOP: 681k; R_0402_1005Metric
R_G01, R_G02, R_G03, R_G04, R_G05, R_G06, R_G07, R_G08, R_G09, R_G10, R_G11, R_G12, R_G13, R_G14, R_G15, R_G16, R_G17, R_G18, R_G19, R_G20, R_G21, R_G22, R_G23, R_G24, R_G25, R_G26, R_G27, R_G28, R_G29, R_G30, R_G31, R_G32: 33R; R_0402_1005Metric
R_ILIM: 18k; R_0402_1005Metric
R_ISET: 600R; R_0402_1005Metric
R_LE_PD: 100k; R_0402_1005Metric
R_LE_SER: 22R; R_0402_1005Metric
R_LOGIC_PD: 100k; R_0402_1005Metric
R_OE_PU: 47k; R_0402_1005Metric
R_OE_YPU: 47k; R_0402_1005Metric
R_PU01, R_PU02, R_PU03, R_PU04, R_PU05, R_PU06, R_PU07, R_PU08, R_PU09, R_PU10, R_PU11, R_PU12, R_PU13, R_PU14, R_PU15, R_PU16, R_PU17, R_PU18, R_PU19, R_PU20, R_PU21, R_PU22, R_PU23, R_PU24, R_PU25, R_PU26, R_PU27, R_PU28, R_PU29, R_PU30, R_PU31, R_PU32: 47k; R_0402_1005Metric
R_QOD: 1k; R_0402_1005Metric
R_SDI_PD: 100k; R_0402_1005Metric
R_SDI_SER: 22R; R_0402_1005Metric
R_USB_N: 22R; R_0402_1005Metric
R_USB_P: 22R; R_0402_1005Metric
R_XOE: 10k; R_0402_1005Metric
SW1: KMR2; SW_Push_1P1T_NO_CK_KMR2
TH_PCB: NTC10K; R_0402_1005Metric
TP1: AON_3V3; R_0402_1005Metric
TP2: GND; R_0402_1005Metric
U1: ESP32-S3FN8; QFN-56-1EP_7x7mm_P0.4mm_EP5.6x5.6mm
U_AUDIO: TLV9001; SOT-353_SC-70-5
U_AUDIO_SW: TPS22917; SOT-23-6
U_CHG: BQ25185; Texas_DLH0010A_WSON-10-1EP_2x2mm_P0.4mm_EP0.9x1.5mm
U_DEC_A: 74HC154; TSSOP-24_4.4x7.8mm_P0.65mm
U_DEC_B: 74HC154; TSSOP-24_4.4x7.8mm_P0.65mm
U_ESD: USBLC6-2SC6; SOT-23-6
U_GAUGE: MAX17048; Texas_DSG0008A_WSON-8-1EP_2x2mm_P0.5mm_EP0.9x1.6mm
U_IMU: BMI270; Bosch_LGA-14_3x2.5mm_P0.5mm
U_LDO: TPS7A2033; SOT-23-5
U_LED1, U_LED2: MBI5124GP-B; SSOP-24_3.9x8.7mm_P0.635mm
U_LED_BUF: SN74LV125A; TSSOP-14_4.4x5mm_P0.65mm
U_LED_LOGIC: TPS22917; SOT-23-6
U_LED_PWR: TPS63802DLAR; TDFN-10-1EP_2x3mm_P0.5mm_EP0.9x2mm
U_ROW_XLAT: SN74LVC8T245; VQFN-24-1EP_4x4mm_P0.5mm_EP2.5x2.5mm
Y1: L327S400H11L; Crystal_SMD_3225-4Pin_3.2x2.5mm

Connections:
AON_3V3: C_LDO_OUT.1, C_MCU1.1, R_BOOT0.1, R_CHIP_PU.1, R_OE_PU.2, R_XOE.1, TP1.1, TP1.2, U1.2, U1.3, U1.20, U1.29, U1.46, U1.55, U1.56, U_AUDIO_SW.1, U_IMU.5, U_IMU.8, U_LDO.5, U_LED_LOGIC.1, U_ROW_XLAT.1, U_ROW_XLAT.2
AUDIO_EN: R_AUD_PD.1, U1.48, U_AUDIO_SW.3
BAT_RAW: C_CHG_BAT.2, J_BAT.1, U_CHG.2
CHIP_PU: C_CHIP_PU.1, R_CHIP_PU.2, U1.4
COL_01: J_COL.1, U_LED1.5
COL_02: J_COL.2, U_LED1.6
COL_03: J_COL.3, U_LED1.7
COL_04: J_COL.4, U_LED1.8
COL_05: J_COL.5, U_LED1.9
COL_06: J_COL.6, U_LED1.10
COL_07: J_COL.7, U_LED1.11
COL_08: J_COL.8, U_LED1.12
COL_09: J_COL.9, U_LED1.13
COL_10: J_COL.10, U_LED1.14
COL_11: J_COL.11, U_LED1.15
COL_12: J_COL.12, U_LED1.16
COL_13: J_COL.13, U_LED1.17
COL_14: J_COL.14, U_LED1.18
COL_15: J_COL.15, U_LED1.19
COL_16: J_COL.16, U_LED1.20
COL_17: J_COL.17, U_LED2.5
COL_18: J_COL.18, U_LED2.6
COL_19: J_COL.19, U_LED2.7
COL_20: J_COL.20, U_LED2.8
COL_21: J_COL.21, U_LED2.9
COL_22: J_COL.22, U_LED2.10
COL_23: J_COL.23, U_LED2.11
COL_24: J_COL.24, U_LED2.12
COL_25: J_COL.25, U_LED2.13
COL_26: J_COL.26, U_LED2.14
COL_27: J_COL.27, U_LED2.15
COL_28: J_COL.28, U_LED2.16
COL_29: J_COL.29, U_LED2.17
COL_30: J_COL.30, U_LED2.18
COL_31: J_COL.31, U_LED2.19
COL_32: J_COL.32, U_LED2.20
DEC_A_EN_N: RP12.1, U1.39, U_ROW_XLAT.7
DEC_A_EN_N_4V: R_ENA.1, U_DEC_A.18, U_ROW_XLAT.17
DEC_B_EN_N: RP13.1, U1.40, U_ROW_XLAT.8
DEC_B_EN_N_4V: R_ENB.1, U_DEC_B.18, U_ROW_XLAT.16
GND: C_CHG_BAT.1, C_CHG_IN.2, C_CHG_SYS.1, C_CHIP_PU.2, C_LDO_IN.1, C_LDO_OUT.2, C_LED1.2, C_LED2.2, C_MCU1.2, C_SYS.2, C_USB1.2, C_XTAL1.2, C_XTAL2.2, J_BAT.3, J_USB.A1, J_USB.A12, J_USB.B1, J_USB.B12, J_USB.SH, R_ADDR0.2, R_ADDR1.2, R_ADDR2.2, R_ADDR3.2, R_AUD_PD.2, R_CLK_PD.2, R_EN_PD.2, R_EXT1.2, R_EXT2.2, R_FB_BOT.2, R_ILIM.2, R_ISET.2, R_LE_PD.2, R_LOGIC_PD.2, R_SDI_PD.2, SW1.2, TP2.1, U1.11, U1.32, U1.44, U1.45, U1.57, U_AUDIO_SW.2, U_CHG.4, U_CHG.5, U_CHG.11, U_DEC_A.12, U_DEC_A.19, U_DEC_B.12, U_DEC_B.19, U_ESD.2, U_ESD.4, U_ESD.5, U_IMU.6, U_IMU.7, U_LDO.2, U_LED1.1, U_LED2.1, U_LED_BUF.1, U_LED_BUF.4, U_LED_BUF.7, U_LED_BUF.10, U_LED_BUF.13, U_LED_LOGIC.2, U_LED_PWR.2, U_LED_PWR.3, U_LED_PWR.8, U_LED_PWR.11, U_ROW_XLAT.9, U_ROW_XLAT.10, U_ROW_XLAT.11, U_ROW_XLAT.12, U_ROW_XLAT.13, Y1.2, Y1.4
GPIO0_BOOT: R_BOOT0.2, SW1.1, U1.5
ILIM_VSET: R_ILIM.1, U_CHG.7
IMU_INT1: RP03.1, U1.15, U_IMU.4
IMU_SCL: RP02.1, U1.14, U_IMU.13
IMU_SDA: RP01.1, U1.13, U_IMU.14
ISET: R_ISET.1, U_CHG.8
LED_4V1: C_LED1.1, C_LED2.1, Q_ROW01.2, Q_ROW02.2, Q_ROW03.2, Q_ROW04.2, Q_ROW05.2, Q_ROW06.2, Q_ROW07.2, Q_ROW08.2, Q_ROW09.2, Q_ROW10.2, Q_ROW11.2, Q_ROW12.2, Q_ROW13.2, Q_ROW14.2, Q_ROW15.2, Q_ROW16.2, Q_ROW17.2, Q_ROW18.2, Q_ROW19.2, Q_ROW20.2, Q_ROW21.2, Q_ROW22.2, Q_ROW23.2, Q_ROW24.2, Q_ROW25.2, Q_ROW26.2, Q_ROW27.2, Q_ROW28.2, Q_ROW29.2, Q_ROW30.2, Q_ROW31.2, Q_ROW32.2, R_ENA.2, R_ENB.2, R_FB_TOP.1, R_PU01.2, R_PU02.2, R_PU03.2, R_PU04.2, R_PU05.2, R_PU06.2, R_PU07.2, R_PU08.2, R_PU09.2, R_PU10.2, R_PU11.2, R_PU12.2, R_PU13.2, R_PU14.2, R_PU15.2, R_PU16.2, R_PU17.2, R_PU18.2, R_PU19.2, R_PU20.2, R_PU21.2, R_PU22.2, R_PU23.2, R_PU24.2, R_PU25.2, R_PU26.2, R_PU27.2, R_PU28.2, R_PU29.2, R_PU30.2, R_PU31.2, R_PU32.2, U_DEC_A.24, U_DEC_B.24, U_LED_PWR.6, U_ROW_XLAT.23, U_ROW_XLAT.24
LED_CLK: RP04.1, R_CLK_PD.1, U1.18, U_LED_BUF.2
LED_CLK_PRE: R_CLK_SER.1, U_LED_BUF.3
LED_CLK_Y: R_CLK_SER.2, U_LED1.3, U_LED2.3
LED_EN: RP15.1, R_EN_PD.1, U1.41, U_LED_PWR.1
LED_FB: R_FB_BOT.1, R_FB_TOP.2, U_LED_PWR.4
LED_LE: RP06.1, R_LE_PD.1, U1.21, U_LED_BUF.9
LED_LE_PRE: R_LE_SER.1, U_LED_BUF.8
LED_LE_Y: R_LE_SER.2, U_LED1.4, U_LED2.4
LED_LOGIC_3V3: R_OE_YPU.2, R_QOD.2, U_LED1.24, U_LED2.24, U_LED_BUF.14, U_LED_LOGIC.6
LED_LOGIC_EN: RP16.1, R_LOGIC_PD.1, U1.42, U_LED_LOGIC.3
LED_OE_N: RP07.1, R_OE_PU.1, U1.22, U_LED_BUF.12
LED_OE_Y: R_OE_YPU.1, U_LED1.21, U_LED2.21, U_LED_BUF.11
LED_QOD: R_QOD.1, U_LED_LOGIC.5
LED_SDI: RP05.1, R_SDI_PD.1, U1.19, U_LED_BUF.5
LED_SDI_PRE: R_SDI_SER.1, U_LED_BUF.6
LED_SDI_Y: R_SDI_SER.2, U_LED1.2
LED_SDO: U_LED1.22, U_LED2.2
REXT1: R_EXT1.1, U_LED1.23
REXT2: R_EXT2.1, U_LED2.23
ROW_01_ANODE: J_ROW.1, Q_ROW01.3
ROW_01_GATE: Q_ROW01.1, R_G01.1, R_PU01.1
ROW_01_Y: R_G01.2, U_DEC_A.1
ROW_02_ANODE: J_ROW.2, Q_ROW02.3
ROW_02_GATE: Q_ROW02.1, R_G02.1, R_PU02.1
ROW_02_Y: R_G02.2, U_DEC_A.2
ROW_03_ANODE: J_ROW.3, Q_ROW03.3
ROW_03_GATE: Q_ROW03.1, R_G03.1, R_PU03.1
ROW_03_Y: R_G03.2, U_DEC_A.3
ROW_04_ANODE: J_ROW.4, Q_ROW04.3
ROW_04_GATE: Q_ROW04.1, R_G04.1, R_PU04.1
ROW_04_Y: R_G04.2, U_DEC_A.4
ROW_05_ANODE: J_ROW.5, Q_ROW05.3
ROW_05_GATE: Q_ROW05.1, R_G05.1, R_PU05.1
ROW_05_Y: R_G05.2, U_DEC_A.5
ROW_06_ANODE: J_ROW.6, Q_ROW06.3
ROW_06_GATE: Q_ROW06.1, R_G06.1, R_PU06.1
ROW_06_Y: R_G06.2, U_DEC_A.6
ROW_07_ANODE: J_ROW.7, Q_ROW07.3
ROW_07_GATE: Q_ROW07.1, R_G07.1, R_PU07.1
ROW_07_Y: R_G07.2, U_DEC_A.7
ROW_08_ANODE: J_ROW.8, Q_ROW08.3
ROW_08_GATE: Q_ROW08.1, R_G08.1, R_PU08.1
ROW_08_Y: R_G08.2, U_DEC_A.8
ROW_09_ANODE: J_ROW.9, Q_ROW09.3
ROW_09_GATE: Q_ROW09.1, R_G09.1, R_PU09.1
ROW_09_Y: R_G09.2, U_DEC_A.9
ROW_10_ANODE: J_ROW.10, Q_ROW10.3
ROW_10_GATE: Q_ROW10.1, R_G10.1, R_PU10.1
ROW_10_Y: R_G10.2, U_DEC_A.10
ROW_11_ANODE: J_ROW.11, Q_ROW11.3
ROW_11_GATE: Q_ROW11.1, R_G11.1, R_PU11.1
ROW_11_Y: R_G11.2, U_DEC_A.11
ROW_12_ANODE: J_ROW.12, Q_ROW12.3
ROW_12_GATE: Q_ROW12.1, R_G12.1, R_PU12.1
ROW_12_Y: R_G12.2, U_DEC_A.13
ROW_13_ANODE: J_ROW.13, Q_ROW13.3
ROW_13_GATE: Q_ROW13.1, R_G13.1, R_PU13.1
ROW_13_Y: R_G13.2, U_DEC_A.14
ROW_14_ANODE: J_ROW.14, Q_ROW14.3
ROW_14_GATE: Q_ROW14.1, R_G14.1, R_PU14.1
ROW_14_Y: R_G14.2, U_DEC_A.15
ROW_15_ANODE: J_ROW.15, Q_ROW15.3
ROW_15_GATE: Q_ROW15.1, R_G15.1, R_PU15.1
ROW_15_Y: R_G15.2, U_DEC_A.16
ROW_16_ANODE: J_ROW.16, Q_ROW16.3
ROW_16_GATE: Q_ROW16.1, R_G16.1, R_PU16.1
ROW_16_Y: R_G16.2, U_DEC_A.17
ROW_17_ANODE: J_ROW.17, Q_ROW17.3
ROW_17_GATE: Q_ROW17.1, R_G17.1, R_PU17.1
ROW_17_Y: R_G17.2, U_DEC_B.1
ROW_18_ANODE: J_ROW.18, Q_ROW18.3
ROW_18_GATE: Q_ROW18.1, R_G18.1, R_PU18.1
ROW_18_Y: R_G18.2, U_DEC_B.2
ROW_19_ANODE: J_ROW.19, Q_ROW19.3
ROW_19_GATE: Q_ROW19.1, R_G19.1, R_PU19.1
ROW_19_Y: R_G19.2, U_DEC_B.3
ROW_20_ANODE: J_ROW.20, Q_ROW20.3
ROW_20_GATE: Q_ROW20.1, R_G20.1, R_PU20.1
ROW_20_Y: R_G20.2, U_DEC_B.4
ROW_21_ANODE: J_ROW.21, Q_ROW21.3
ROW_21_GATE: Q_ROW21.1, R_G21.1, R_PU21.1
ROW_21_Y: R_G21.2, U_DEC_B.5
ROW_22_ANODE: J_ROW.22, Q_ROW22.3
ROW_22_GATE: Q_ROW22.1, R_G22.1, R_PU22.1
ROW_22_Y: R_G22.2, U_DEC_B.6
ROW_23_ANODE: J_ROW.23, Q_ROW23.3
ROW_23_GATE: Q_ROW23.1, R_G23.1, R_PU23.1
ROW_23_Y: R_G23.2, U_DEC_B.7
ROW_24_ANODE: J_ROW.24, Q_ROW24.3
ROW_24_GATE: Q_ROW24.1, R_G24.1, R_PU24.1
ROW_24_Y: R_G24.2, U_DEC_B.8
ROW_25_ANODE: J_ROW.25, Q_ROW25.3
ROW_25_GATE: Q_ROW25.1, R_G25.1, R_PU25.1
ROW_25_Y: R_G25.2, U_DEC_B.9
ROW_26_ANODE: J_ROW.26, Q_ROW26.3
ROW_26_GATE: Q_ROW26.1, R_G26.1, R_PU26.1
ROW_26_Y: R_G26.2, U_DEC_B.10
ROW_27_ANODE: J_ROW.27, Q_ROW27.3
ROW_27_GATE: Q_ROW27.1, R_G27.1, R_PU27.1
ROW_27_Y: R_G27.2, U_DEC_B.11
ROW_28_ANODE: J_ROW.28, Q_ROW28.3
ROW_28_GATE: Q_ROW28.1, R_G28.1, R_PU28.1
ROW_28_Y: R_G28.2, U_DEC_B.13
ROW_29_ANODE: J_ROW.29, Q_ROW29.3
ROW_29_GATE: Q_ROW29.1, R_G29.1, R_PU29.1
ROW_29_Y: R_G29.2, U_DEC_B.14
ROW_30_ANODE: J_ROW.30, Q_ROW30.3
ROW_30_GATE: Q_ROW30.1, R_G30.1, R_PU30.1
ROW_30_Y: R_G30.2, U_DEC_B.15
ROW_31_ANODE: J_ROW.31, Q_ROW31.3
ROW_31_GATE: Q_ROW31.1, R_G31.1, R_PU31.1
ROW_31_Y: R_G31.2, U_DEC_B.16
ROW_32_ANODE: J_ROW.32, Q_ROW32.3
ROW_32_GATE: Q_ROW32.1, R_G32.1, R_PU32.1
ROW_32_Y: R_G32.2, U_DEC_B.17
ROW_A0: RP08.1, U1.23, U_ROW_XLAT.3
ROW_A0_4V: R_ADDR0.1, U_DEC_A.23, U_DEC_B.23, U_ROW_XLAT.21
ROW_A1: RP09.1, U1.24, U_ROW_XLAT.4
ROW_A1_4V: R_ADDR1.1, U_DEC_A.22, U_DEC_B.22, U_ROW_XLAT.20
ROW_A2: RP10.1, U1.27, U_ROW_XLAT.5
ROW_A2_4V: R_ADDR2.1, U_DEC_A.21, U_DEC_B.21, U_ROW_XLAT.19
ROW_A3: RP11.1, U1.38, U_ROW_XLAT.6
ROW_A3_4V: R_ADDR3.1, U_DEC_A.20, U_DEC_B.20, U_ROW_XLAT.18
ROW_XLAT_OE_N: RP14.1, R_XOE.2, U1.37, U_ROW_XLAT.22
SW_L1: L_LED.2, U_LED_PWR.9
SW_L2: L_LED.1, U_LED_PWR.7
SYS: C_CHG_SYS.2, C_LDO_IN.2, C_SYS.1, U_CHG.1, U_LDO.1, U_LDO.3, U_LED_PWR.10
TS_MR: J_BAT.2, U_CHG.6
USB_D_N: J_USB.A7, J_USB.B7, R_USB_N.1, U_ESD.3
USB_D_N_MCU: R_USB_N.2, U1.25
USB_D_P: J_USB.A6, J_USB.B6, R_USB_P.1, U_ESD.1, U_ESD.6
USB_D_P_MCU: R_USB_P.2, U1.26
VBUS: C_CHG_IN.1, C_USB1.1, J_USB.A4, J_USB.A9, J_USB.B4, J_USB.B9, U_CHG.10
XTAL_N: C_XTAL2.1, U1.53, Y1.3
XTAL_P: C_XTAL1.1, U1.54, Y1.1
